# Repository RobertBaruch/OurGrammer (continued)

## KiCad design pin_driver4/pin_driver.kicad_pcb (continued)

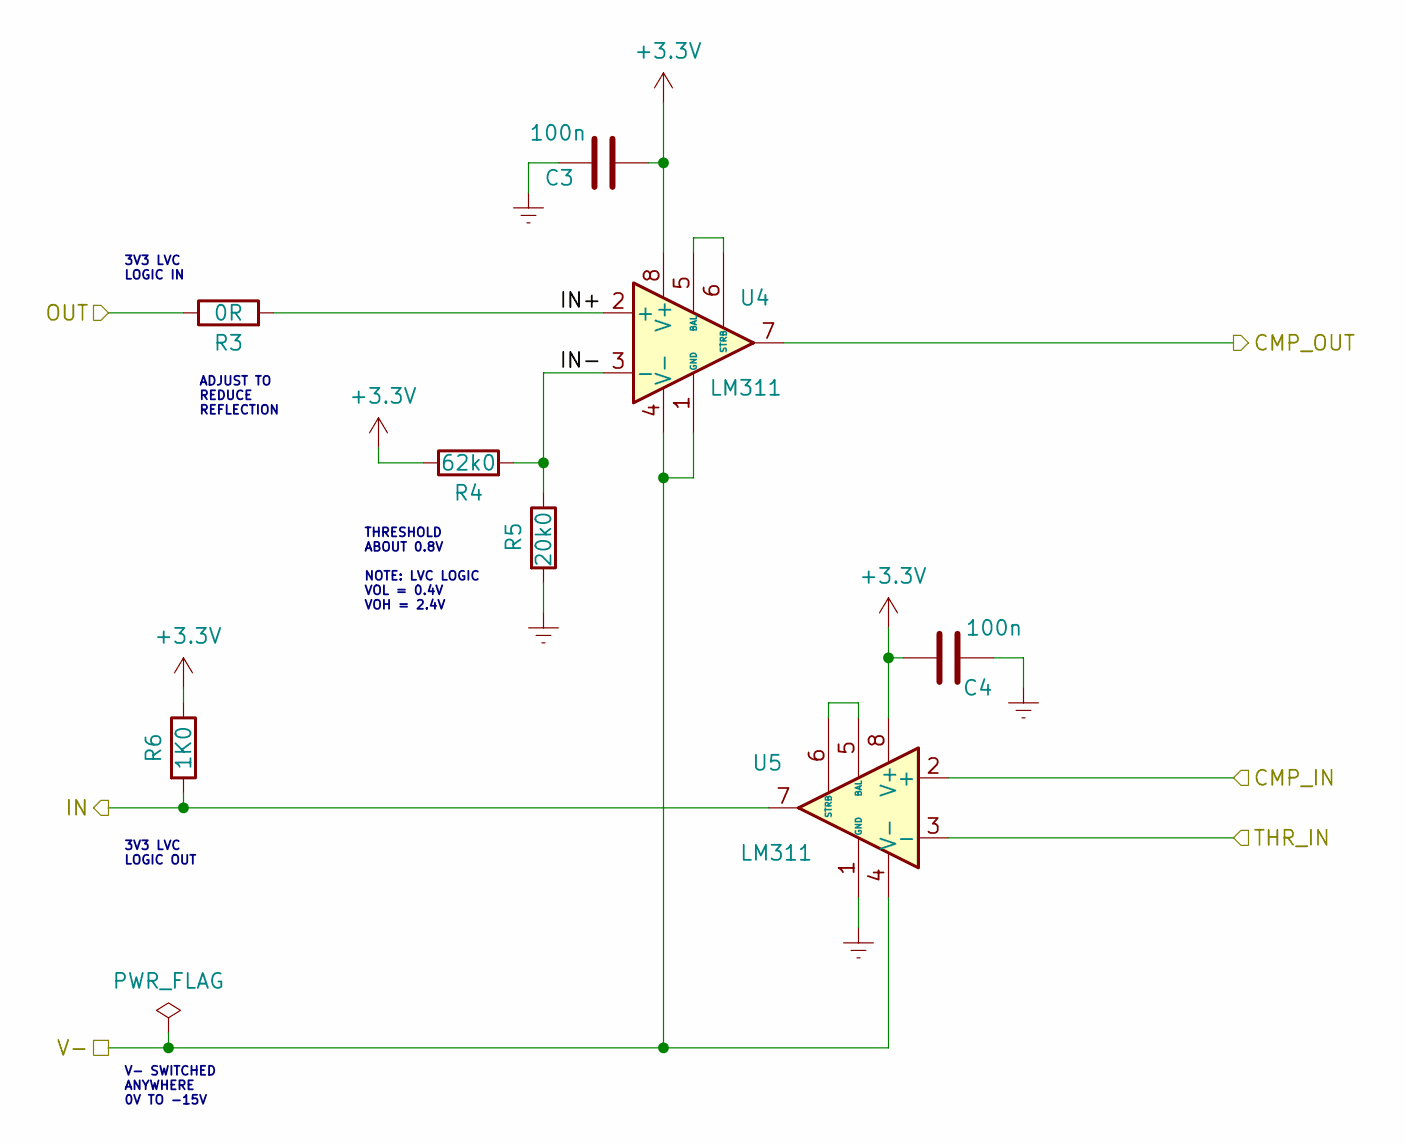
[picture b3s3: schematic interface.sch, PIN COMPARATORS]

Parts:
C3, C4: 100n; C_0603_1608Metric
R3: 0R; R_0603_1608Metric
R4: 62k0; R_0603_1608Metric
R5: 20k0; R_0603_1608Metric
R6: 1K0; R_0603_1608Metric
U4, U5: LM311; SO-8_3.9x4.9mm_P1.27mm

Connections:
+3V3: C3.1, C4.1, R4.1, R6.1, U4.8 (V+), U5.8 (V+); also elsewhere on the board
/IN: R6.2, U5.7; also elsewhere on the board
/Interface/IN+: R3.2, U4.2 (+)
/Interface/IN-: R4.2, R5.1, U4.3 (-)
/OUT: R3.1; also elsewhere on the board
/PIN: U5.2 (+); also elsewhere on the board
/SIG_OUT: U4.7; also elsewhere on the board
/VT: U5.3 (-); also elsewhere on the board
GNDREF: C3.2, C4.2, R5.2, U5.1 (GND); also elsewhere on the board
unnamed: U4.5 (BAL), U4.6 (STRB)
unnamed: U5.5 (BAL), U5.6 (STRB)
VS: U4.1 (GND), U4.4 (V-), U5.4 (V-); also elsewhere on the board

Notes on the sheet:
THRESHOLD ABOUT 0.8V NOTE: LVC LOGIC VOL = 0.4V VOH = 2.4V
ADJUST TO REDUCE REFLECTION
3V3 LVC LOGIC IN
V- SWITCHED ANYWHERE 0V TO -15V
3V3 LVC LOGIC OUT

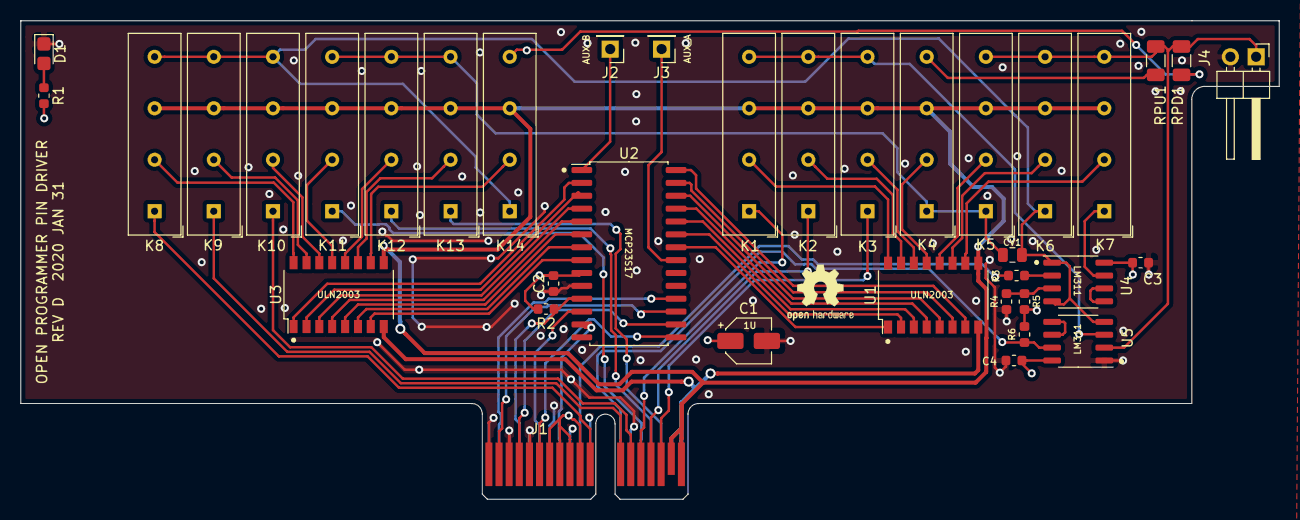
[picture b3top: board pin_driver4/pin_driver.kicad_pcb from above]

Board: 4 copper layers, 124.2 x 47.2 mm, 37 parts (0 on the bottom side), 64 nets.

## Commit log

2020-05-23 Dump
